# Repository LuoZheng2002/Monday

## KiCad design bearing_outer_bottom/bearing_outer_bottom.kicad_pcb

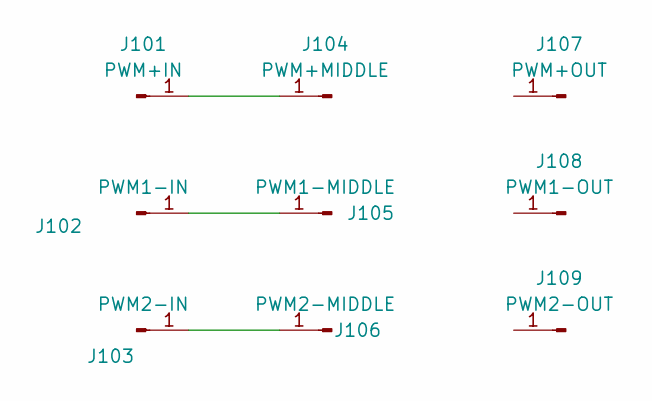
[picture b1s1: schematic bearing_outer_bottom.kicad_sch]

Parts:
J101: PWM+IN; MyPinSocket
J102: PWM1-IN; MyPinSocket
J103: PWM2-IN; MyPinSocket
J104: PWM+MIDDLE; my_small_pad
J105: PWM1-MIDDLE; my_small_pad
J106: PWM2-MIDDLE; my_small_pad
J107: PWM+OUT; my_small_pad
J108: PWM1-OUT; my_small_pad
J109: PWM2-OUT; my_small_pad

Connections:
unnamed: J101.1, J104.1
unnamed: J102.1, J105.1
unnamed: J103.1, J106.1

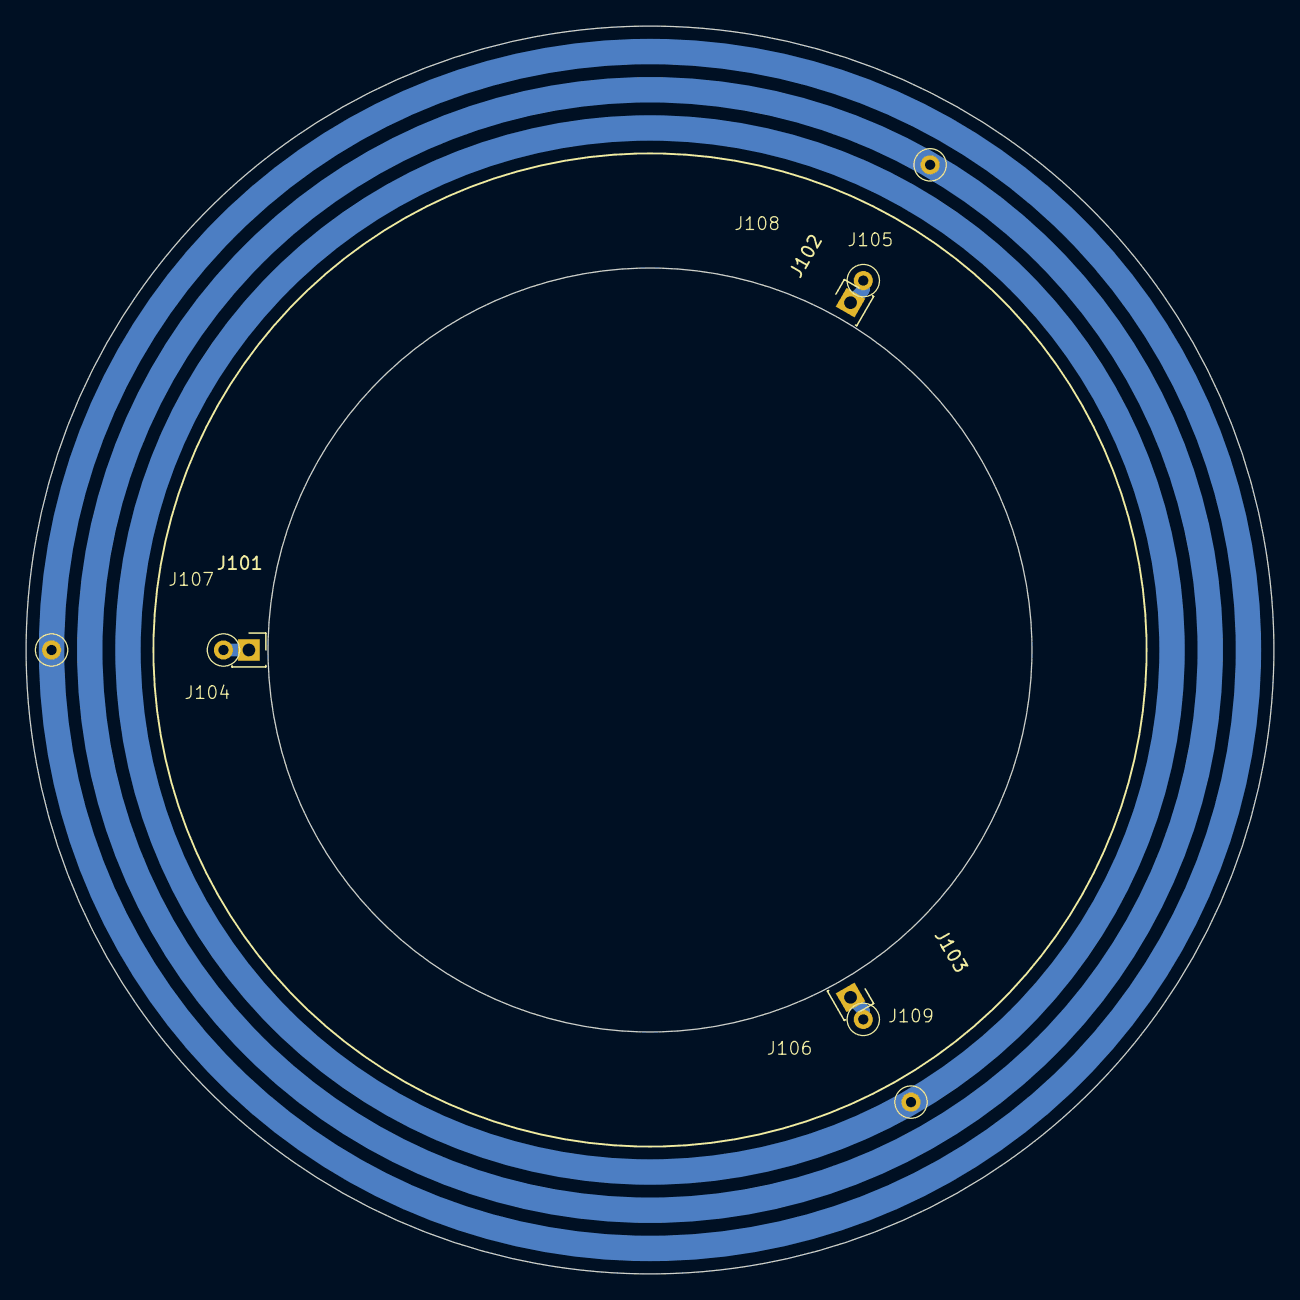
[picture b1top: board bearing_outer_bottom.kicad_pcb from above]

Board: 2 copper layers, 98.0 x 98.0 mm, 9 parts (0 on the bottom side), 3 nets.

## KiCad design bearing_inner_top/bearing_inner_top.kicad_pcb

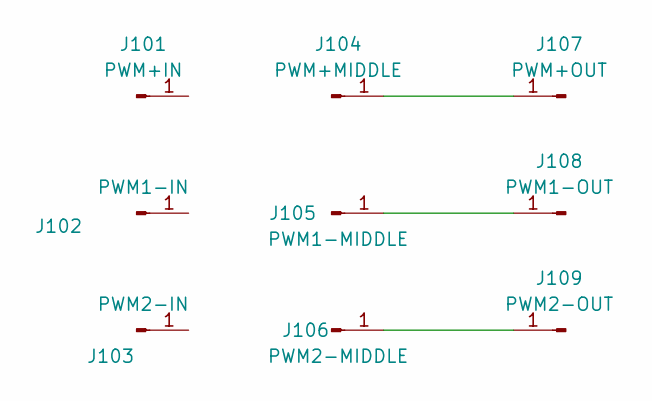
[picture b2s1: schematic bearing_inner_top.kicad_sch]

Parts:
J101: PWM+IN; MyPinSocket
J102: PWM1-IN; MyPinSocket
J103: PWM2-IN; MyPinSocket
J104: PWM+MIDDLE; my_small_pad
J105: PWM1-MIDDLE; my_small_pad
J106: PWM2-MIDDLE; my_small_pad
J107: PWM+OUT; my_small_pad
J108: PWM1-OUT; my_small_pad
J109: PWM2-OUT; my_small_pad

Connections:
unnamed: J104.1, J107.1
unnamed: J105.1, J108.1
unnamed: J106.1, J109.1

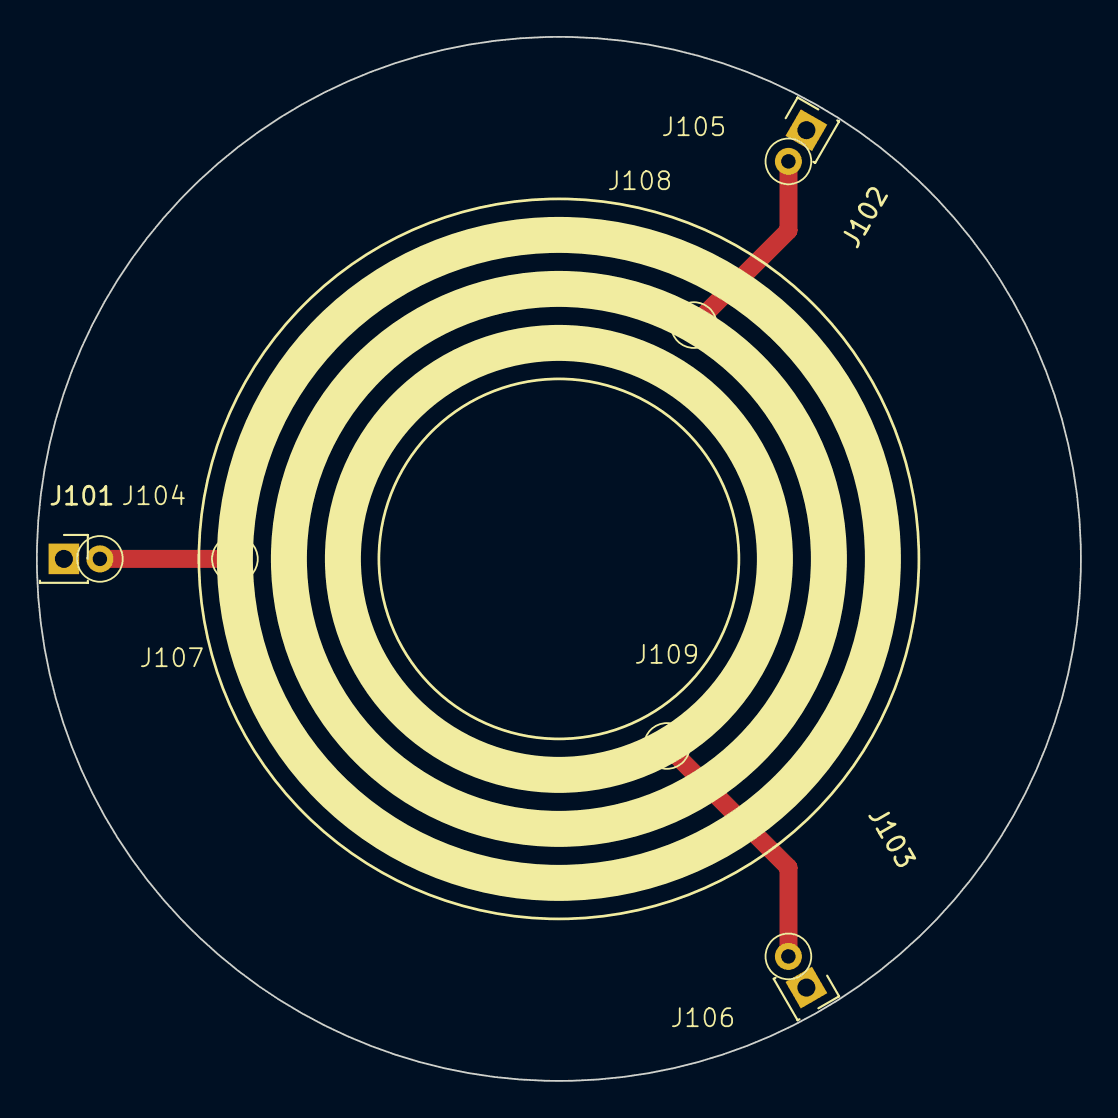
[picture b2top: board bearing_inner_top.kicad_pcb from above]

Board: 2 copper layers, 58.0 x 58.0 mm, 9 parts (0 on the bottom side), 3 nets.

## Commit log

2024-02-12 checkpoint
